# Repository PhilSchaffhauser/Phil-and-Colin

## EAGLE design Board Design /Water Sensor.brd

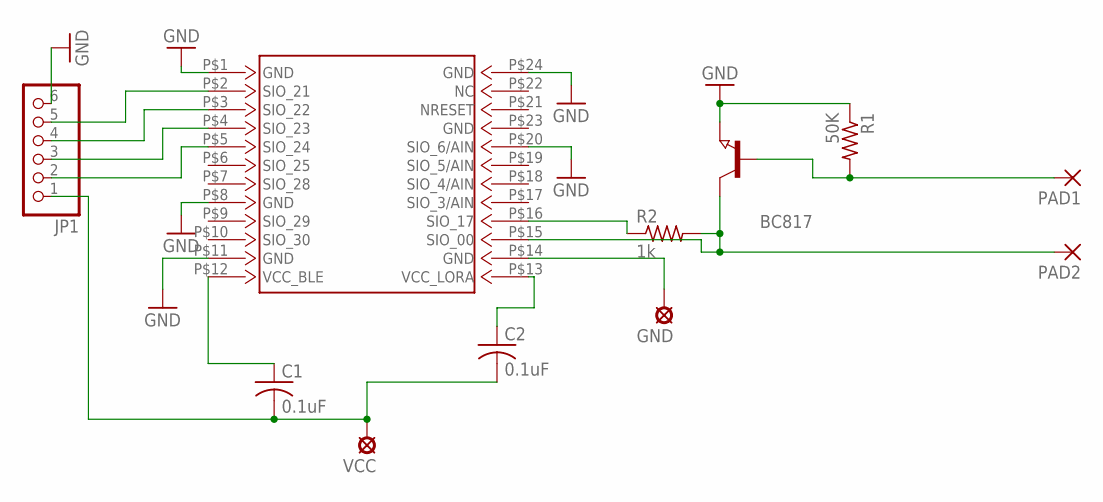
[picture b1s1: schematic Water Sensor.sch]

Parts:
BC817: NPN-TRANSISTOR_SOT23; SOT23
C1, C2: 0.1uF; C0805
GND: SE13
JP1: PINHD-1X6; 1X06
PAD1, PAD2: SMD5; SMD2,54-5,08
R1: 50K; M0805
R2: 1k; M0805
RM191: RM191RM1XX; RM191
VCC: SE13

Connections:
GND: BC817.2 (E), GND.MP, JP1.6, R1.1, RM191.P$1 (GND), RM191.P$8 (GND), RM191.P$11 (GND), RM191.P$14 (GND), RM191.P$20 (SIO_6/AIN), RM191.P$24 (GND)
unnamed: JP1.5, RM191.P$2 (SIO_21)
unnamed: BC817.1 (B), PAD1.1, R1.2
unnamed: R2.1, RM191.P$16 (SIO_17)
unnamed: C2.1, RM191.P$13 (VCC_LORA)
unnamed: JP1.4, RM191.P$3 (SIO_22)
unnamed: BC817.3 (C), PAD2.1, R2.2, RM191.P$15 (SIO_00)
unnamed: JP1.3, RM191.P$4 (SIO_23)
unnamed: JP1.2, RM191.P$5 (SIO_24)
unnamed: C1.1, RM191.P$12 (VCC_BLE)
unnamed: C1.2, C2.2, JP1.1, VCC.MP

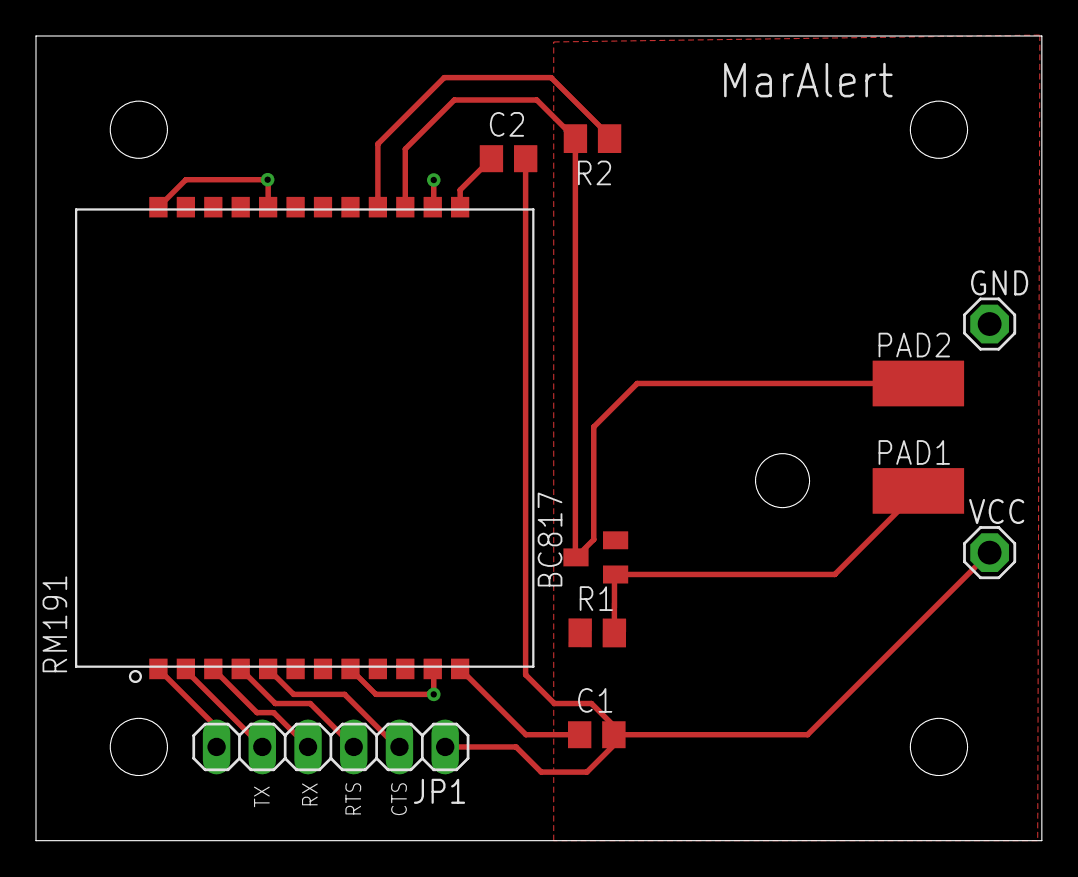
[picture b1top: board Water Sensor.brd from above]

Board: 2 copper layers, 55.9 x 44.7 mm, 11 parts (0 on the bottom side), 11 nets.

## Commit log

2018-04-04 Firmware
2018-04-04 board design
2018-04-05 added smartBasic test code
    
    ``
2018-04-13 board files
2018-04-13 Board design files
